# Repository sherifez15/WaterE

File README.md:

# WaterE
This is a modified version of my senior project design. The project is a smart water meter that can communicate with an API and send data. Advanced version of this design includes a remote controlled solenoid valve that receives commands over IP as well.

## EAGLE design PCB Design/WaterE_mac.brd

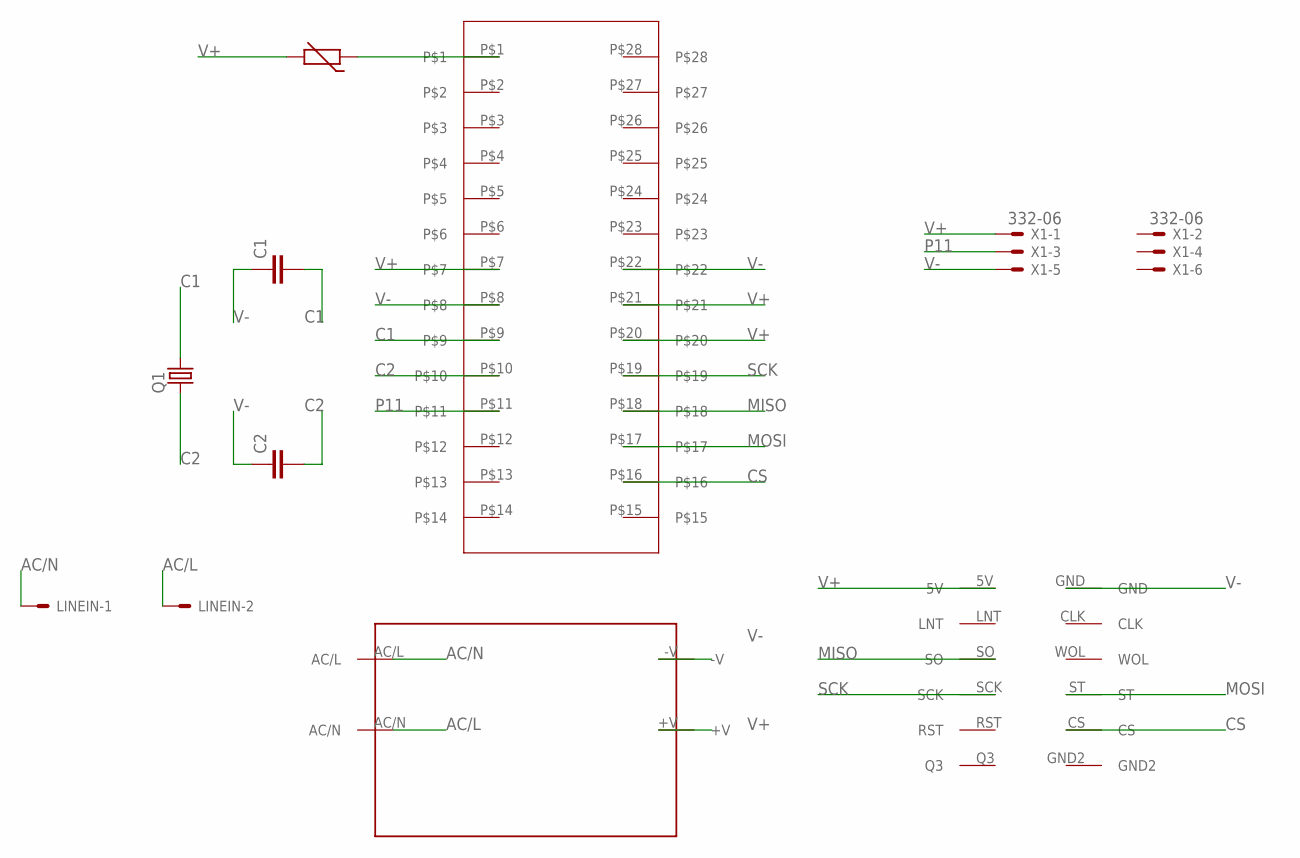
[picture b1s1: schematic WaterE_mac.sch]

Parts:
C1, C2: C-EU025-024X044; C025-024X044
LINEIN: AC/L; 332-02
Q1: CRYSTALTC26V; TC26V
R1: THERMISTOR_R-5; R-5
U$1: POWER_COMPONENT
U$2: ETHER
U$4: SOCKET_SENIOR
X1: 332-06

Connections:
AC/L: LINEIN.2, U$1.AC/N
AC/N: LINEIN.1, U$1.AC/L
C1: C1.2, Q1.2, U$4.P$9
C2: C2.2, Q1.1, U$4.P$10
CS: U$2.CS, U$4.P$16
MISO: U$2.SO, U$4.P$18
MOSI: U$2.ST, U$4.P$17
unnamed: R1.1, U$4.P$1
P11: U$4.P$11, X1.3
SCK: U$2.SCK, U$4.P$19
V+: R1.2, U$1.+V, U$2.5V, U$4.P$7, U$4.P$20, U$4.P$21, X1.1
V-: C1.1, C2.1, U$1.-V, U$2.GND, U$4.P$8, U$4.P$22, X1.5

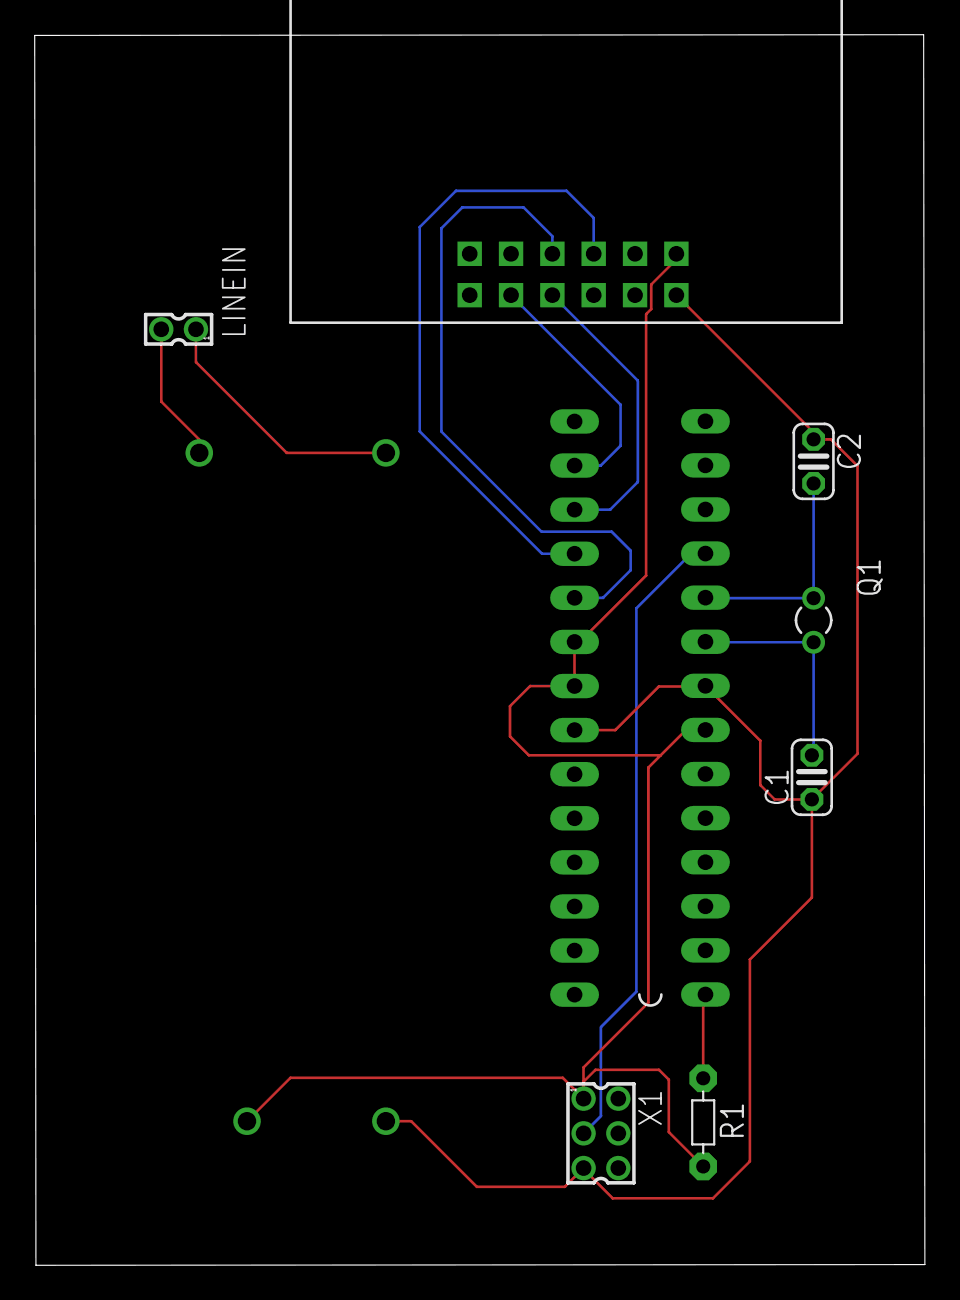
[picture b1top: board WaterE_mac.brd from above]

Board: 2 copper layers, 51.3 x 70.9 mm, 9 parts (1 on the bottom side), 12 nets.
